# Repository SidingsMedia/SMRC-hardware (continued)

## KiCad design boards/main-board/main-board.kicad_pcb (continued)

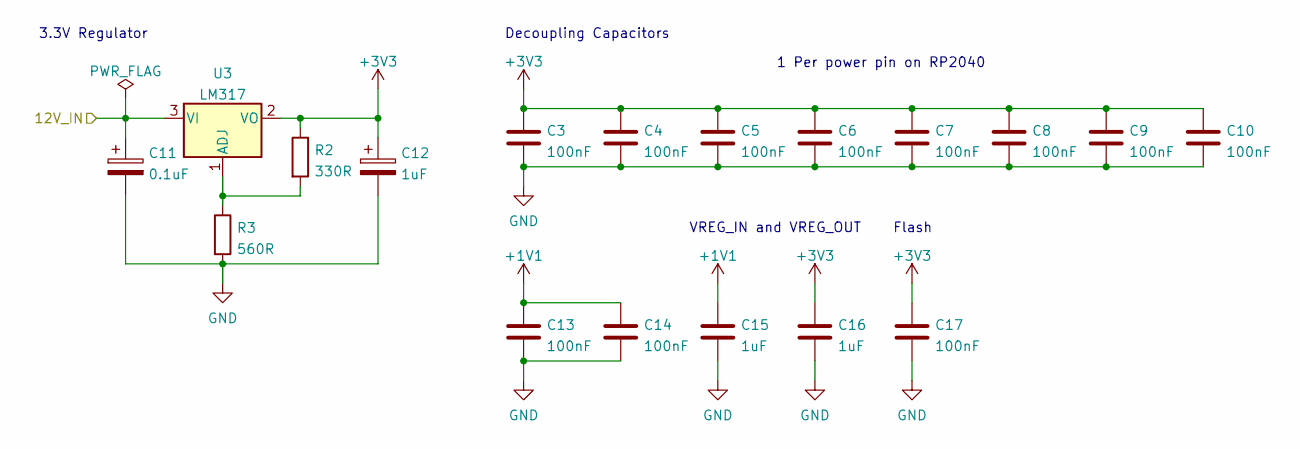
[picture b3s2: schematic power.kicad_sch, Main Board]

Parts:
C3, C4, C5, C6, C7, C8, C9, C10, C13, C14, C17: 100nF; C_0805_2012Metric
C11: 0.1uF; CP_Elec_4x3
C12: 1uF; CP_Elec_4x3
C15, C16: 1uF; C_0805_2012Metric
R2: 330R; R_0805_2012Metric
R3: 560R; R_0805_2012Metric
U3: LM317; SOT-223-3_TabPin2

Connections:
+1V1: C13.1, C14.1, C15.1; also elsewhere on the board
+3V3: C3.1, C4.1, C5.1, C6.1, C7.1, C8.1, C9.1, C10.1, C12.1, C16.1, C17.1, R2.1, U3.2 (VO); also elsewhere on the board
/Power/12V_IN: C11.1, U3.3 (VI); also elsewhere on the board
GND: C3.2, C4.2, C5.2, C6.2, C7.2, C8.2, C9.2, C10.2, C11.2, C12.2, C13.2, C14.2, C15.2, C16.2, C17.2, R3.2; also elsewhere on the board
unnamed: R2.2, R3.1, U3.1 (ADJ)

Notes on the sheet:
Decoupling Capacitors
VREG_IN and VREG_OUT
3.3V Regulator
Flash
1 Per power pin on RP2040

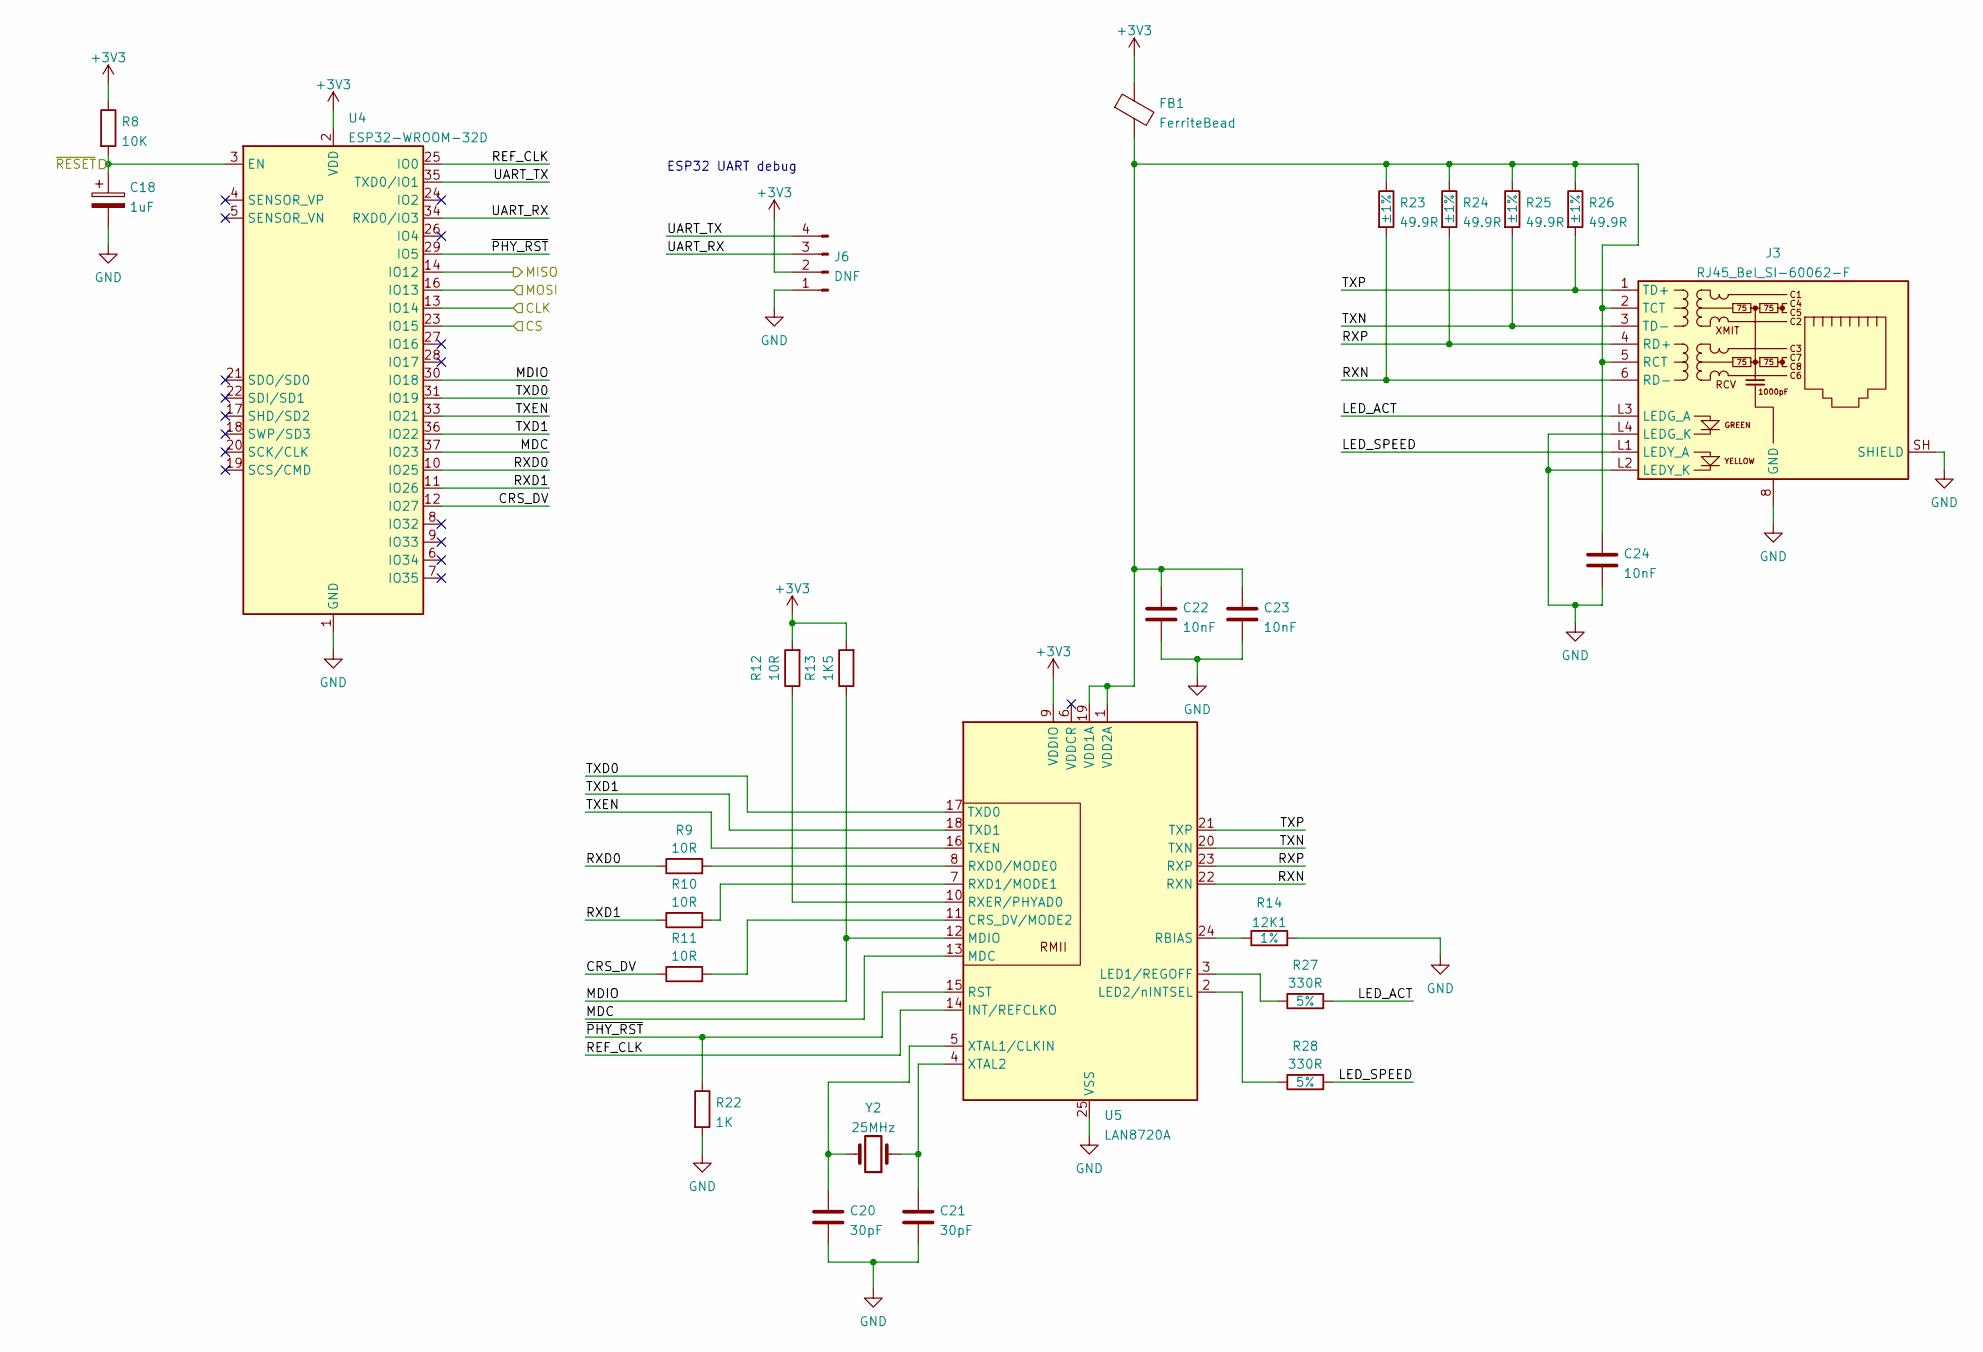
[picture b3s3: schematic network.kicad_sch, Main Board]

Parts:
C18: 1uF; CP_Elec_4x3
C20, C21: 30pF; C_0805_2012Metric
C22, C23, C24: 10nF; C_0805_2012Metric
FB1: FerriteBead; R_0805_2012Metric
J3: RJ45_Bel_SI-60062-F
J6: DNF; PinHeader_1x04_P2.54mm_Vertical
R8: 10K; R_0805_2012Metric
R9, R10, R11, R12: 10R; R_0805_2012Metric
R13: 1K5; R_0805_2012Metric
R14: 12K1; R_0805_2012Metric; Tolerance 1%
R22: 1K; R_0805_2012Metric
R23, R24, R25, R26: 49.9R; R_0805_2012Metric; Tolerance ±1%
R27, R28: 330R; R_0805_2012Metric; Tolerance 5%
U4: ESP32-WROOM-32D; ESP32-WROOM-32
U5: LAN8720A; QFN-24-1EP_4x4mm_P0.5mm_EP2.6x2.6mm
Y2: 25MHz; Crystal_SMD_HC49-SD

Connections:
+3V3: FB1.1, J6.2, R8.1, R12.2, R13.2, U4.2 (VDD), U5.9 (VDDIO); also elsewhere on the board
/NET_CLK: U4.13 (IO14); also elsewhere on the board
/NET_CS: U4.23 (IO15); also elsewhere on the board
/NET_MISO: U4.14 (IO12); also elsewhere on the board
/NET_MOSI: U4.16 (IO13); also elsewhere on the board
/Network/CRS_DV: R11.1, U4.12 (IO27)
/Network/LED_ACT: J3.L3 (LEDG_A), R27.2
/Network/LED_SPEED: J3.L1 (LEDY_A), R28.2
/Network/MDC: U4.37 (IO23), U5.13 (MDC)
/Network/MDIO: R13.1, U4.30 (IO18), U5.12 (MDIO)
/Network/REF_CLK: U4.25 (IO0), U5.14 (INT/REFCLKO)
/Network/RXD0: R9.1, U4.10 (IO25)
/Network/RXD1: R10.1, U4.11 (IO26)
/Network/RXN: J3.6 (RD-), R23.2, U5.22 (RXN)
/Network/RXP: J3.4 (RD+), R24.2, U5.23 (RXP)
/Network/TXD0: U4.31 (IO19), U5.17 (TXD0)
/Network/TXD1: U4.36 (IO22), U5.18 (TXD1)
/Network/TXEN: U4.33 (IO21), U5.16 (TXEN)
/Network/TXN: J3.3 (TD-), R25.2, U5.20 (TXN)
/Network/TXP: J3.1 (TD+), R26.2, U5.21 (TXP)
/Network/UART_RX: J6.3, U4.34 (RXD0/IO3)
/Network/UART_TX: J6.4, U4.35 (TXD0/IO1)
/Network/~PHY_RST: R22.1, U4.29 (IO5), U5.15 (RST)
/~RST: C18.1, R8.2, U4.3 (EN); also elsewhere on the board
GND: C18.2, C20.2, C21.2, C22.2, C23.2, C24.2, J3.8 (GND), J3.L2 (LEDY_K), J3.L4 (LEDG_K), J3.SH (SHIELD), J6.1, R14.2, R22.2, U4.1 (GND), U4.15 (GND), U4.38 (GND), U4.39 (GND), U5.25 (VSS); also elsewhere on the board
unnamed: C20.1, U5.5 (XTAL1/CLKIN), Y2.2
unnamed: C21.1, U5.4 (XTAL2), Y2.1
unnamed: C22.1, C23.1, C24.1, FB1.2, J3.2 (TCT), J3.5 (RCT), R23.1, R24.1, R25.1, R26.1, U5.1 (VDD2A), U5.19 (VDD1A)
unnamed: R9.2, U5.8 (RXD0/MODE0)
unnamed: R10.2, U5.7 (RXD1/MODE1)
unnamed: R11.2, U5.11 (CRS_DV/MODE2)
unnamed: R12.1, U5.10 (RXER/PHYAD0)
unnamed: R14.1, U5.24 (RBIAS)
unnamed: R27.1, U5.3 (LED1/REGOFF)
unnamed: R28.1, U5.2 (LED2/nINTSEL)

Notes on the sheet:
ESP32 UART debug

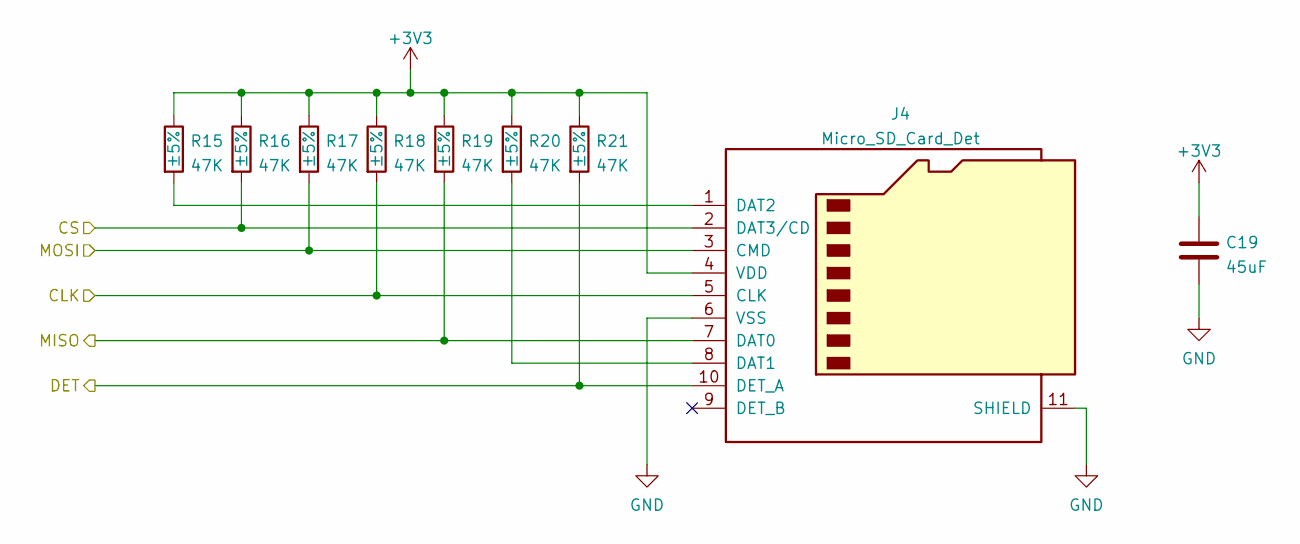
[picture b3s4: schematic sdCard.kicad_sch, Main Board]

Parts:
C19: 45uF; CP_Elec_4x3
J4: Micro_SD_Card_Det; microSD_HC_Molex_104031-0811
R15, R16, R17, R18, R19, R20, R21: 47K; R_0805_2012Metric; Tolerance ±5%

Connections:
+3V3: C19.1, J4.4 (VDD), R15.1, R16.1, R17.1, R18.1, R19.1, R20.1, R21.1; also elsewhere on the board
/SD_CLK: J4.5 (CLK), R18.2; also elsewhere on the board
/SD_CS: J4.2 (DAT3/CD), R16.2; also elsewhere on the board
/SD_DET: J4.10 (DET_A), R21.2; also elsewhere on the board
/SD_MISO: J4.7 (DAT0), R19.2; also elsewhere on the board
/SD_MOSI: J4.3 (CMD), R17.2; also elsewhere on the board
GND: C19.2, J4.6 (VSS), J4.11 (SHIELD); also elsewhere on the board
unnamed: J4.1 (DAT2), R15.2
unnamed: J4.8 (DAT1), R20.2

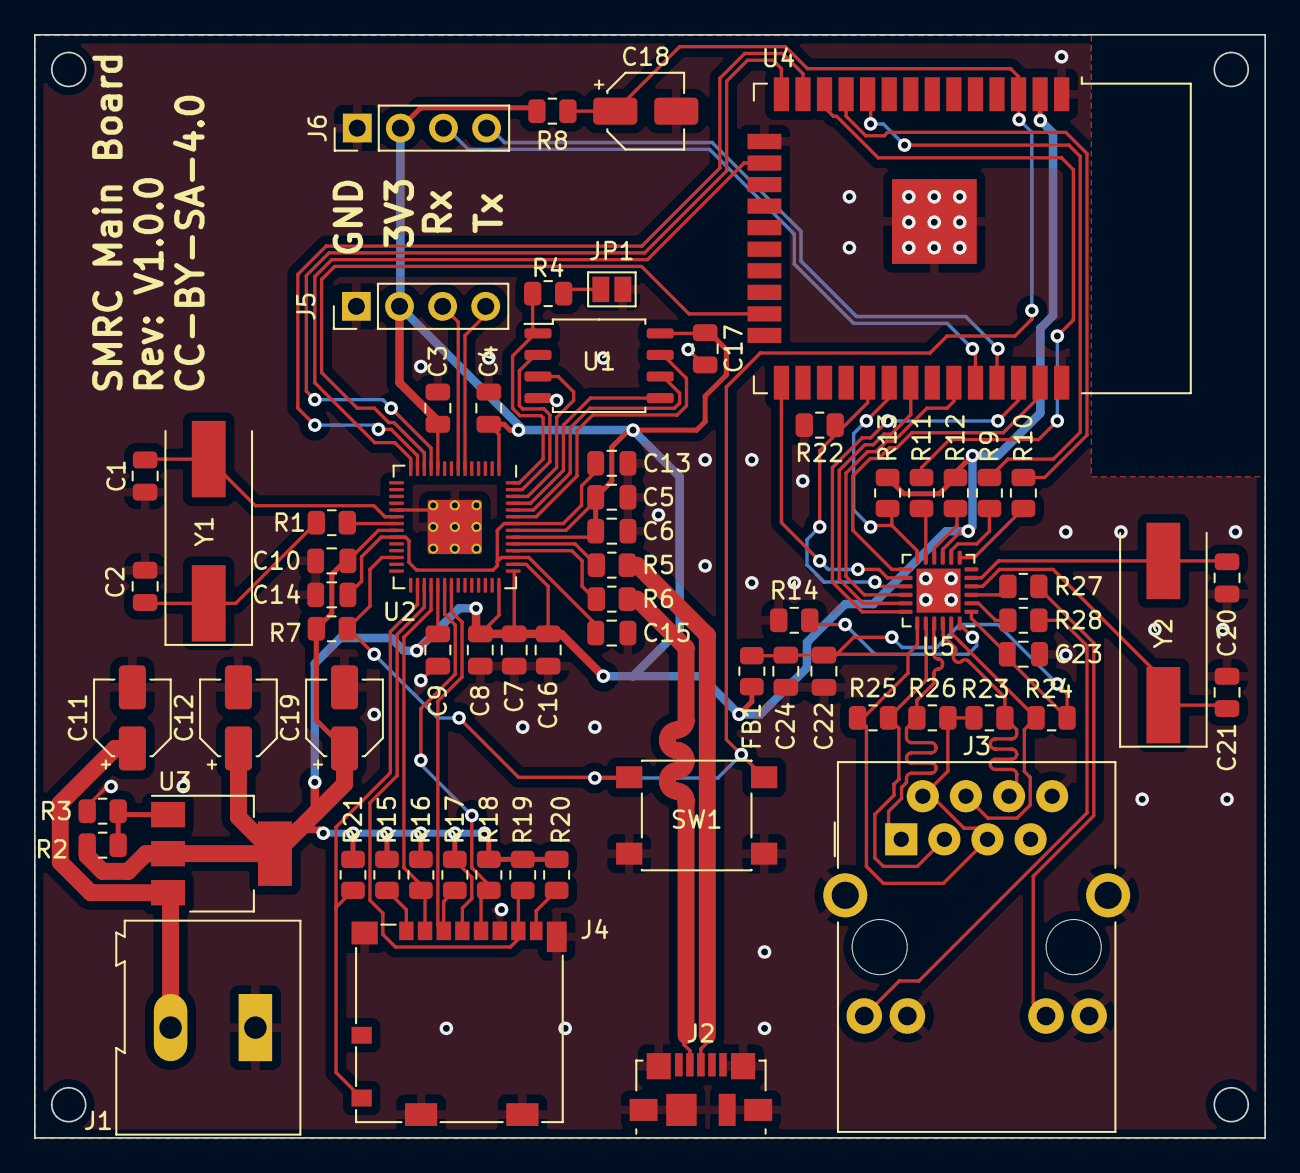
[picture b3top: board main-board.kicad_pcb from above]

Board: 2 copper layers, 72.5 x 65.0 mm, 68 parts (0 on the bottom side), 61 nets.

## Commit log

2021-08-17 Added basic admin files
2021-08-27 Made reuse compliant
2021-08-27 Fixed dep5 files
2021-10-21 Created prettierrc control file
2021-10-21 Added .gitignore
    Ignore rules have been added for kicad files as well as the vscode
    config directory.
2021-10-21 Fixed reuse licence issue for prettierrc
    Commit 18bddbf6aa9a099e063f6a8171a4d9e6cb208fec broke the reuse
    compliance check by not specifying the licence for the file.
2021-10-21 Updated gitignore to include cache lib files
2021-10-21 Added schematic style
    The style for the schematics as well as the licence file for it has been
    added. This file must be used to style all schematics in this repository
2021-10-21 Fixed file extensions
    The licence extensions were not spelt as required by resue and as such
    the compliance checks fail.
2021-10-22 Created initial KiCad project
2022-01-01 Added basic design
2022-01-01 Changed copyright name to Matthew Nickson
2022-01-01 Added component annotations
2022-01-01 Fixed POWER_IN being a global label
2022-01-02 Added preliminary footprints
2022-01-02 Moved to KiCad 6
2022-01-02 Minor updates to values of components
2022-01-02 Fixed REUSE compliance
2022-01-02 Created main-board blank schematic
2022-01-02 Added basic RP2040 schematics
2022-03-18 Version 1.1.0 of main control board schematic
2022-03-19 Moved SPI connections + increment version
2022-03-19 Replaced USB C with micro usb
2022-03-19 Added SD_DET to RP2040
2022-03-19 Fixed resistor connecting to wrong line
2022-03-19 Added resistors for LEDs
2022-03-19 Incremented version number
2022-03-19 PCB V1.0.0
2022-03-19 Added images of boards
2022-03-19 Added USB + assigned footprints
2022-03-19 Changed out LM317 + increment version
2022-03-19 Added annotations
2022-03-19 Removed unnecessary components
2022-03-19 Finished V1.0.0 of driver board PCB
2022-03-19 Added images for speed controller
2022-03-20 Created initial relay schematic
2022-03-20 Added 12V for relays
2022-03-20 Added 12V for regulator
2022-03-20 Changed pin connections for relay channels
2022-03-20 Added Tx and Rx LEDs
2022-03-20 Version 1.0.0 of PCB
2022-03-20 Added image of relay board
2022-03-23 Added readme for each board with BOM
